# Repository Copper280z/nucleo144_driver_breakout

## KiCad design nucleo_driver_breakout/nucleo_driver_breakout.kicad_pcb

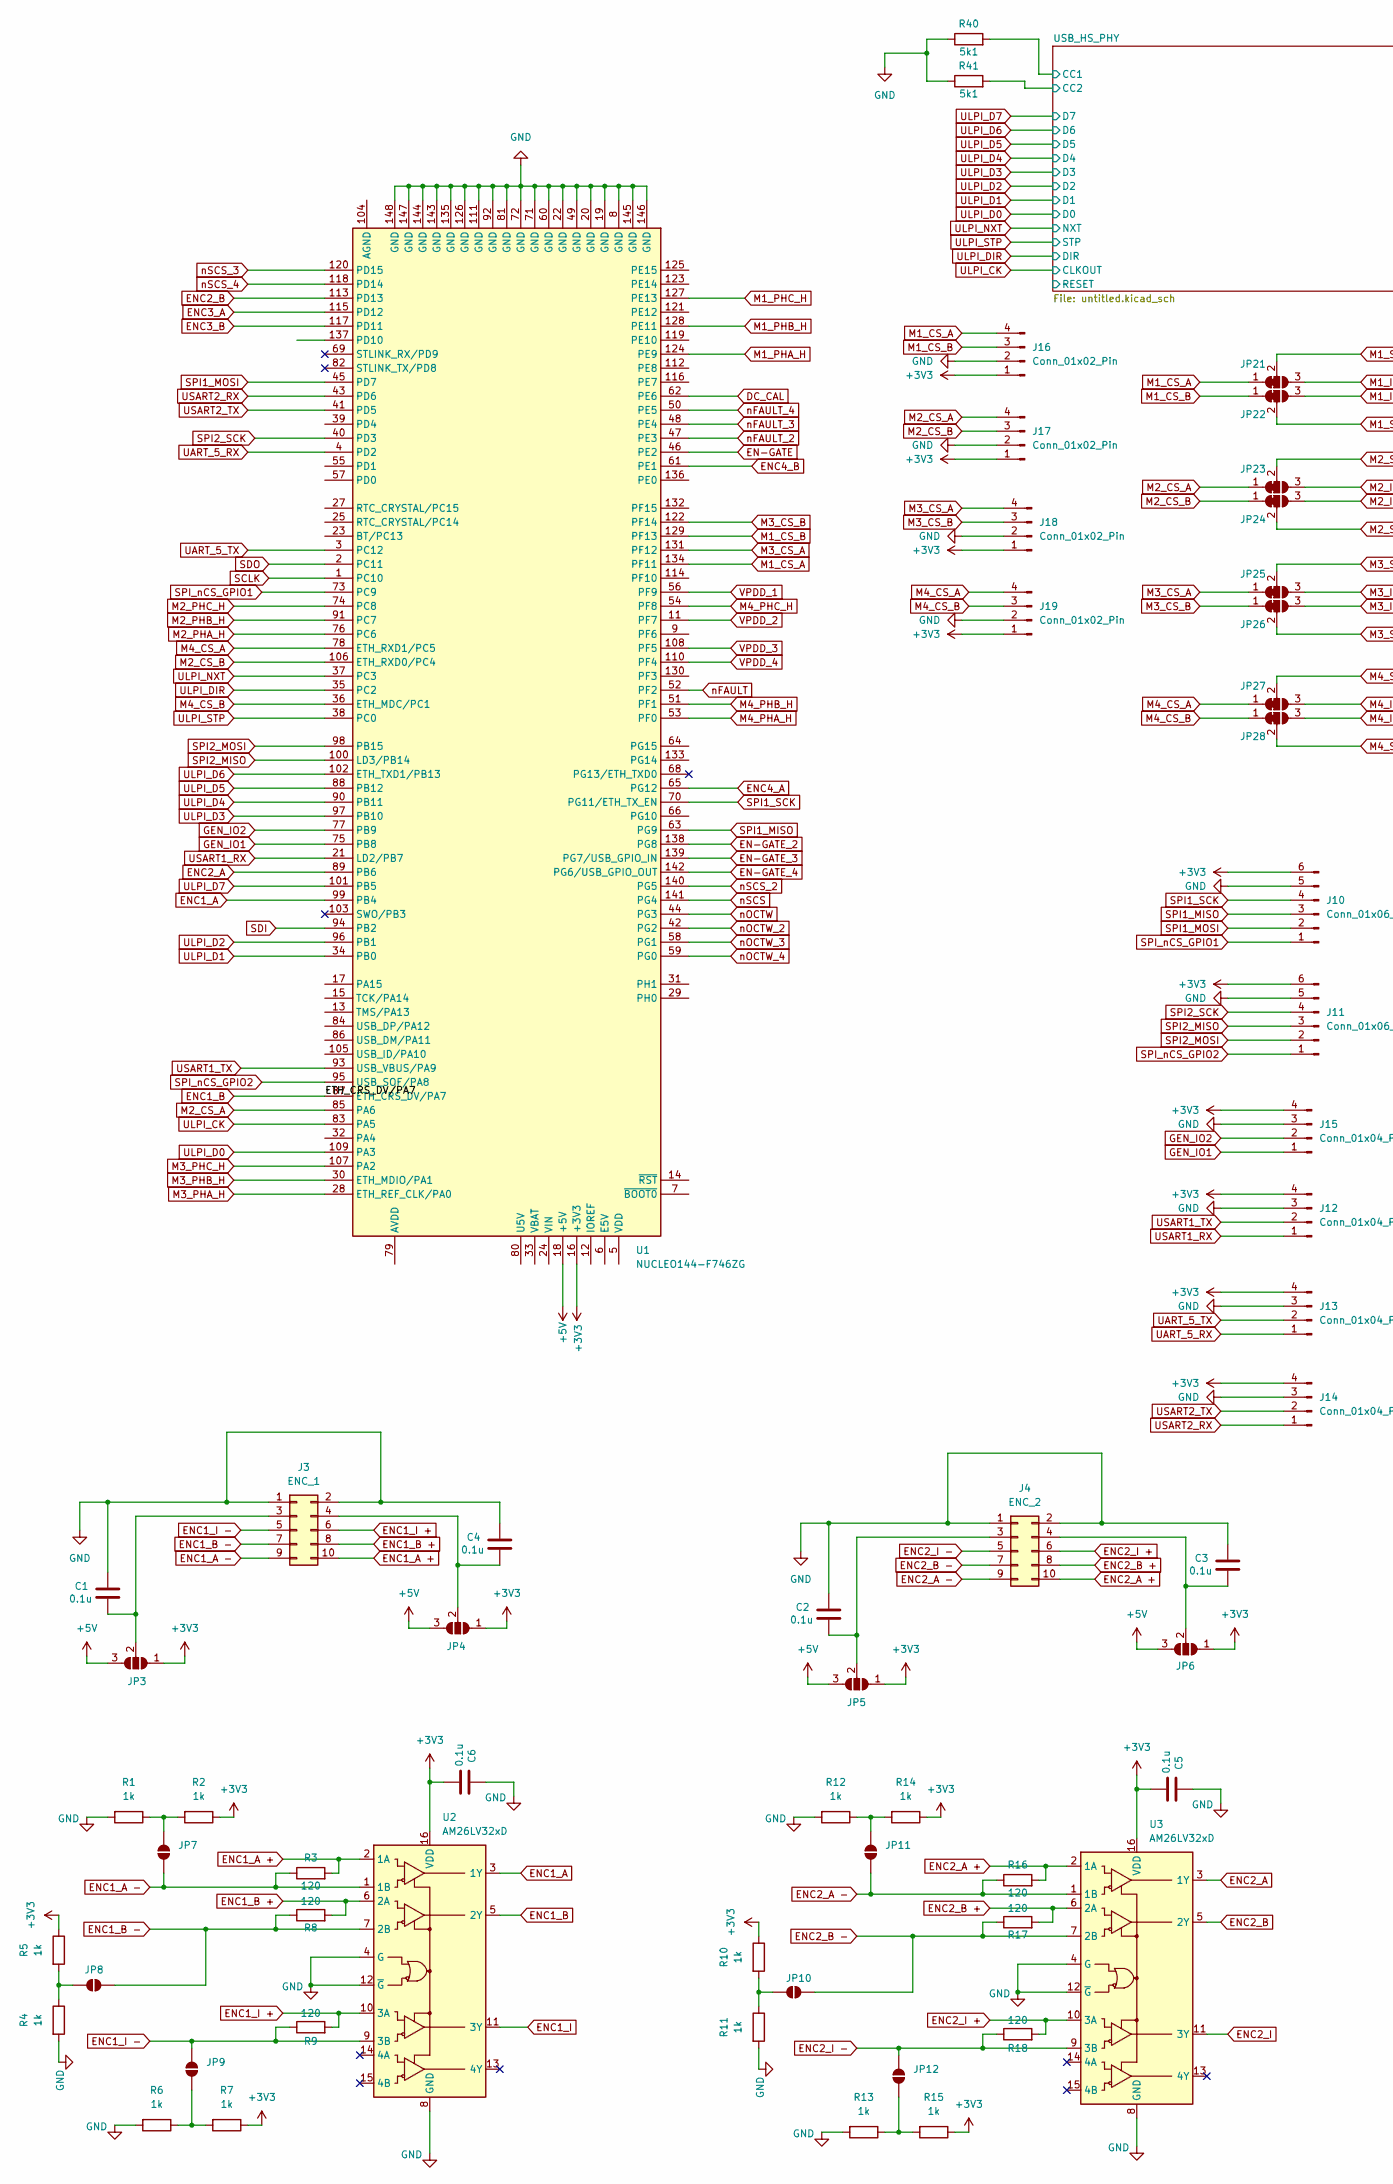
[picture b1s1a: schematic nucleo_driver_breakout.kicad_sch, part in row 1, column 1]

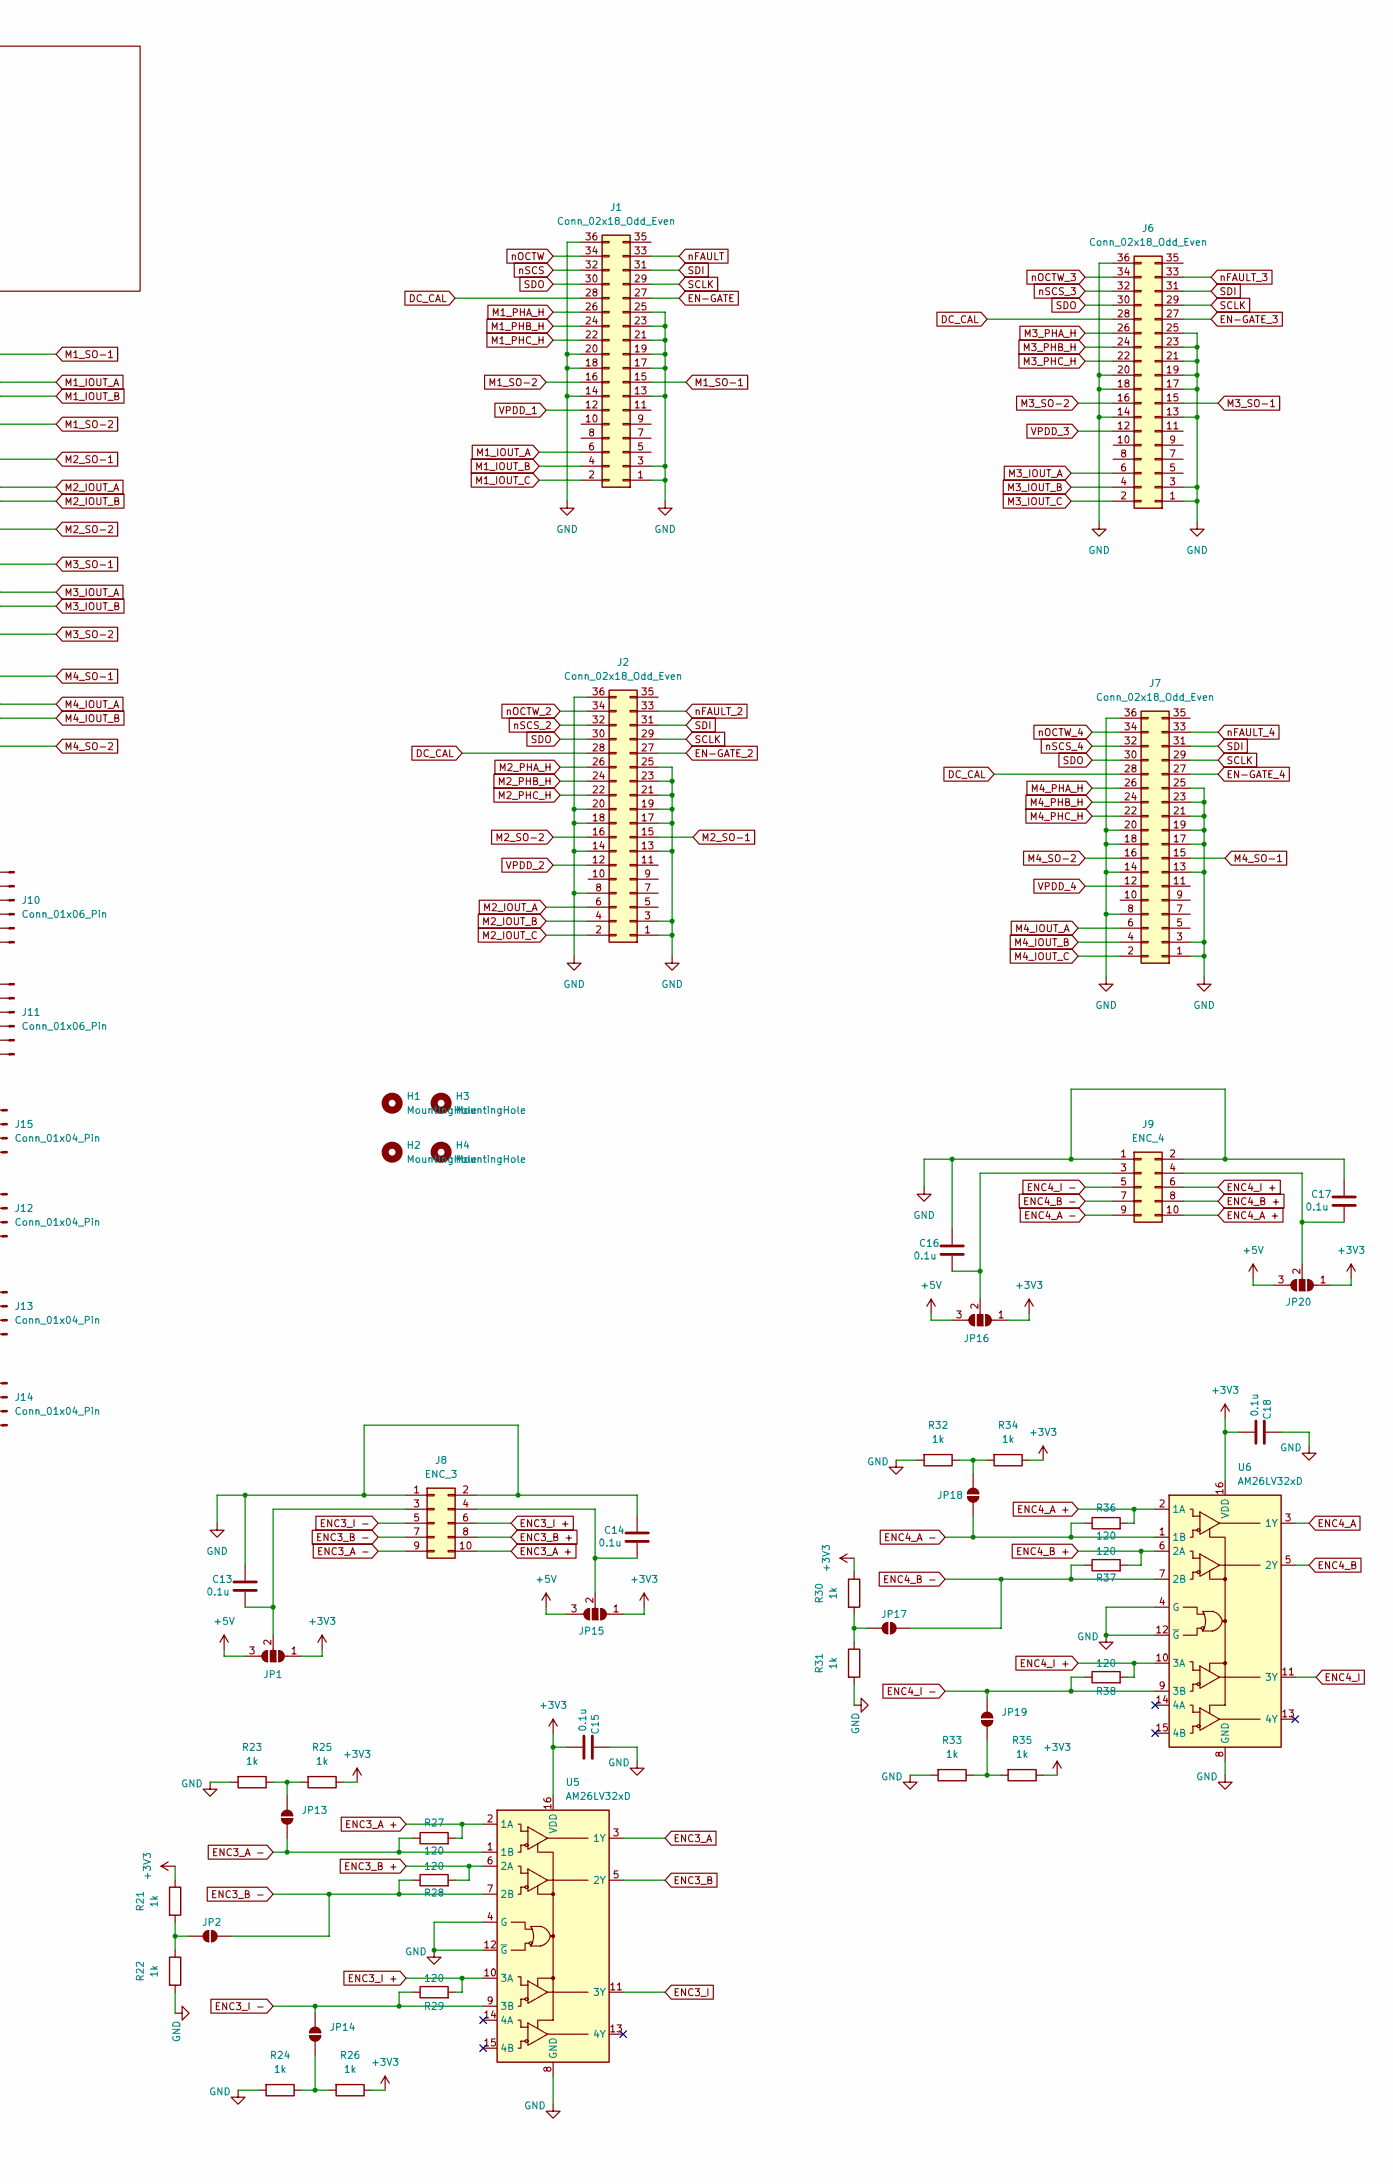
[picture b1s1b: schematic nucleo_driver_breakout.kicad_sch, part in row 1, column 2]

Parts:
C1, C2, C3, C4, C5, C6, C13, C14, C15, C16, C17, C18: 0.1u; C_0402_1005Metric; LCSC ID C1525
H1, H2, H3, H4: MountingHole; MountingHole_3.2mm_M3_ISO7380
J1, J2, J6, J7: Conn_02x18_Odd_Even; PinHeader_2x18_P2.54mm_Vertical
J3: ENC_1; PinHeader_2x05_P2.54mm_Vertical
J4: ENC_2; PinHeader_2x05_P2.54mm_Vertical
J8: ENC_3; PinHeader_2x05_P2.54mm_Vertical
J9: ENC_4; PinHeader_2x05_P2.54mm_Vertical
J10, J11: Conn_01x06_Pin; JST_EH_B6B-EH-A_1x06_P2.50mm_Vertical
J12, J13, J14, J15: Conn_01x04_Pin; JST_EH_B4B-EH-A_1x04_P2.50mm_Vertical
J16, J17, J18, J19: Conn_01x02_Pin; JST_EH_B4B-EH-A_1x04_P2.50mm_Vertical
JP1, JP3, JP4, JP5, JP6, JP15, JP16, JP20: SolderJumper_3_Open; SolderJumper-3_P1.3mm_Open_RoundedPad1.0x1.5mm
JP2, JP7, JP8, JP9, JP10, JP11, JP12, JP13, JP14, JP17, JP18, JP19: SolderJumper_2_Open; SolderJumper-2_P1.3mm_Open_RoundedPad1.0x1.5mm
JP21, JP22, JP23, JP24, JP25, JP26, JP27, JP28: SolderJumper_3_Bridged12; SolderJumper-3_P1.3mm_Bridged12_RoundedPad1.0x1.5mm
R1, R2, R4, R5, R6, R7, R10, R11, R12, R13, R14, R15, R21, R22, R23, R24, R25, R26, R30, R31, R32, R33, R34, R35: 1k; R_0402_1005Metric; LCSC ID C11702
R3, R8, R9, R16, R17, R18, R27, R28, R29, R36, R37, R38: 120; R_1206_3216Metric; LCSC ID C17909
R40: 5k1; R_0402_1005Metric; LCSC ID C25079
R41: 5k1; R_0402_1005Metric; LCSC ID C25905
U1: NUCLEO144-F746ZG; ST_Morpho_Connector_144_STLink
U2, U3, U5, U6: AM26LV32xD; SOIC-16_3.9x9.9mm_P1.27mm; LCSC ID C524786

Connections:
+3V3: C5.2, C6.2, C15.2, C18.2, J10.6, J11.6, J12.4, J13.4, J14.4, J15.4, J16.1, J17.1, J18.1, J19.1, JP1.1 (A), JP3.1 (A), JP4.1 (A), JP5.1 (A), JP6.1 (A), JP15.1 (A), JP16.1 (A), JP20.1 (A), R2.1, R5.1, R7.1, R10.1, R14.1, R15.1, R21.1, R25.1, R26.1, R30.1, R34.1, R35.1, U1.16 (+3V3), U2.16 (VDD), U3.16 (VDD), U5.16 (VDD), U6.16 (VDD); also elsewhere on the board
+5V: JP1.3 (B), JP3.3 (B), JP4.3 (B), JP5.3 (B), JP6.3 (B), JP15.3 (B), JP16.3 (B), JP20.3 (B), U1.18 (+5V)
/USB_HS_PHY/CC1: R40.2; also elsewhere on the board
/USB_HS_PHY/CC2: R41.2; also elsewhere on the board
DC_CAL: J1.28, J2.28, J6.28, J7.28, U1.62 (PE6)
EN-GATE: J1.27, U1.46 (PE2)
EN-GATE_2: J2.27, U1.138 (PG8)
EN-GATE_3: J6.27, U1.139 (PG7/USB_GPIO_IN)
EN-GATE_4: J7.27, U1.142 (PG6/USB_GPIO_OUT)
ENC1_A: U1.99 (PB4), U2.3 (1Y)
ENC1_A +: J3.10, R3.2, U2.2 (1A)
ENC1_A -: J3.9, JP7.1 (A), R3.1, U2.1 (1B)
ENC1_B: U1.87 (ETH_CRS_DV/PA7), U2.5 (2Y)
ENC1_B +: J3.8, R8.2, U2.6 (2A)
ENC1_B -: J3.7, JP8.1 (A), R8.1, U2.7 (2B)
ENC1_I: U2.11 (3Y)
ENC1_I +: J3.6, R9.2, U2.10 (3A)
ENC1_I -: J3.5, JP9.1 (A), R9.1, U2.9 (3B)
ENC2_A: U1.89 (PB6), U3.3 (1Y)
ENC2_A +: J4.10, R16.2, U3.2 (1A)
ENC2_A -: J4.9, JP11.1 (A), R16.1, U3.1 (1B)
ENC2_B: U1.113 (PD13), U3.5 (2Y)
ENC2_B +: J4.8, R17.2, U3.6 (2A)
ENC2_B -: J4.7, JP10.1 (A), R17.1, U3.7 (2B)
ENC2_I: U3.11 (3Y)
ENC2_I +: J4.6, R18.2, U3.10 (3A)
ENC2_I -: J4.5, JP12.1 (A), R18.1, U3.9 (3B)
ENC3_A: U1.115 (PD12), U5.3 (1Y)
ENC3_A +: J8.10, R27.2, U5.2 (1A)
ENC3_A -: J8.9, JP13.1 (A), R27.1, U5.1 (1B)
ENC3_B: U1.117 (PD11), U5.5 (2Y)
ENC3_B +: J8.8, R28.2, U5.6 (2A)
ENC3_B -: J8.7, JP2.1 (A), R28.1, U5.7 (2B)
ENC3_I: U5.11 (3Y)
ENC3_I +: J8.6, R29.2, U5.10 (3A)
ENC3_I -: J8.5, JP14.1 (A), R29.1, U5.9 (3B)
ENC4_A: U1.65 (PG12), U6.3 (1Y)
ENC4_A +: J9.10, R36.2, U6.2 (1A)
ENC4_A -: J9.9, JP18.1 (A), R36.1, U6.1 (1B)
ENC4_B: U1.61 (PE1), U6.5 (2Y)
ENC4_B +: J9.8, R37.2, U6.6 (2A)
ENC4_B -: J9.7, JP17.1 (A), R37.1, U6.7 (2B)
ENC4_I: U6.11 (3Y)
ENC4_I +: J9.6, R38.2, U6.10 (3A)
ENC4_I -: J9.5, JP19.1 (A), R38.1, U6.9 (3B)
GEN_IO1: J15.1, U1.75 (PB8)
GEN_IO2: J15.2, U1.77 (PB9)
GND: C1.1, C2.1, C3.1, C4.1, C5.1, C6.1, C13.1, C14.1, C15.1, C16.1, C17.1, C18.1, J1.1, J1.3, J1.13, J1.14, J1.17, J1.18, J1.19, J1.20, J1.21, J1.23, J1.25, J1.36, J2.1, J2.3, J2.8, J2.13, J2.14, J2.17, J2.18, J2.19, J2.20, J2.21, J2.23, J2.25, J2.36, J3.1, J3.2, J4.1, J4.2, J6.1, J6.3, J6.13, J6.14, J6.17, J6.18, J6.19, J6.20, J6.21, J6.23, J6.25, J6.36, J7.1, J7.3, J7.8, J7.13, J7.14, J7.17, J7.18, J7.19, J7.20, J7.21, J7.23, J7.25, J7.36, J8.1, J8.2, J9.1, J9.2, J10.5, J11.5, J12.3, J13.3, J14.3, J15.3, J16.2, J17.2, J18.2, J19.2, R1.2, R4.2, R6.2, R11.2, R12.2, R13.2, R22.2, R23.2, R24.2, R31.2, R32.2, R33.2, R40.1, R41.1, U1.8 (GND), U1.19 (GND), U1.20 (GND), U1.22 (GND), U1.49 (GND), U1.60 (GND), U1.71 (GND), U1.72 (GND), U1.81 (GND), U1.92 (GND), U1.111 (GND), U1.126 (GND), U1.135 (GND), U1.143 (GND), U1.144 (GND), U1.145 (GND), U1.146 (GND), U1.147 (GND), U1.148 (GND), U2.4 (G), U2.8 (GND), U2.12 (~G), U3.4 (G), U3.8 (GND), U3.12 (~G), U5.4 (G), U5.8 (GND), U5.12 (~G), U6.4 (G), U6.8 (GND), U6.12 (~G); also elsewhere on the board
M1_CS_A: J16.4, JP21.1 (A), U1.134 (PF11)
M1_CS_B: J16.3, JP22.1 (A), U1.129 (PF13)
M1_IOUT_A: J1.6, JP21.3 (B)
M1_IOUT_B: J1.4, JP22.3 (B)
M1_IOUT_C: J1.2
M1_PHA_H: J1.26, U1.124 (PE9)
M1_PHB_H: J1.24, U1.128 (PE11)
M1_PHC_H: J1.22, U1.127 (PE13)
M1_SO-1: J1.15, JP21.2 (C)
M1_SO-2: J1.16, JP22.2 (C)
M2_CS_A: J17.4, JP23.1 (A), U1.85 (PA6)
M2_CS_B: J17.3, JP24.1 (A), U1.106 (ETH_RXD0/PC4)
M2_IOUT_A: J2.6, JP23.3 (B)
M2_IOUT_B: J2.4, JP24.3 (B)
M2_IOUT_C: J2.2
M2_PHA_H: J2.26, U1.76 (PC6)
M2_PHB_H: J2.24, U1.91 (PC7)
M2_PHC_H: J2.22, U1.74 (PC8)
M2_SO-1: J2.15, JP23.2 (C)
M2_SO-2: J2.16, JP24.2 (C)
M3_CS_A: J18.4, JP25.1 (A), U1.131 (PF12)
M3_CS_B: J18.3, JP26.1 (A), U1.122 (PF14)
M3_IOUT_A: J6.6, JP25.3 (B)
M3_IOUT_B: J6.4, JP26.3 (B)
M3_IOUT_C: J6.2
M3_PHA_H: J6.26, U1.28 (ETH_REF_CLK/PA0)
M3_PHB_H: J6.24, U1.30 (ETH_MDIO/PA1)
M3_PHC_H: J6.22, U1.107 (PA2)
M3_SO-1: J6.15, JP25.2 (C)
M3_SO-2: J6.16, JP26.2 (C)
M4_CS_A: J19.4, JP27.1 (A), U1.78 (ETH_RXD1/PC5)
M4_CS_B: J19.3, JP28.1 (A), U1.36 (ETH_MDC/PC1)
M4_IOUT_A: J7.6, JP27.3 (B)
M4_IOUT_B: J7.4, JP28.3 (B)
M4_IOUT_C: J7.2
M4_PHA_H: J7.26, U1.53 (PF0)
M4_PHB_H: J7.24, U1.51 (PF1)
M4_PHC_H: J7.22, U1.54 (PF8)
M4_SO-1: J7.15, JP27.2 (C)
M4_SO-2: J7.16, JP28.2 (C)
unnamed: C1.2, J3.3, JP3.2 (C)
unnamed: C4.2, J3.4, JP4.2 (C)
unnamed: C2.2, J4.3, JP5.2 (C)
unnamed: C3.2, J4.4, JP6.2 (C)
unnamed: C13.2, J8.3, JP1.2 (C)
unnamed: C14.2, J8.4, JP15.2 (C)
unnamed: C16.2, J9.3, JP16.2 (C)
unnamed: C17.2, J9.4, JP20.2 (C)
unnamed: JP2.2 (B), R21.2, R22.1
unnamed: JP7.2 (B), R1.1, R2.2
unnamed: JP8.2 (B), R4.1, R5.2
unnamed: JP9.2 (B), R6.1, R7.2
unnamed: JP10.2 (B), R10.2, R11.1
unnamed: JP11.2 (B), R12.1, R14.2
unnamed: JP12.2 (B), R13.1, R15.2
unnamed: JP13.2 (B), R23.1, R25.2
unnamed: JP14.2 (B), R24.1, R26.2
unnamed: JP17.2 (B), R30.2, R31.1
unnamed: JP18.2 (B), R32.1, R34.2
unnamed: JP19.2 (B), R33.1, R35.2
SCLK: J1.29, J2.29, J6.29, J7.29, U1.1 (PC10)
SDI: J1.31, J2.31, J6.31, J7.31, U1.94 (PB2)
SDO: J1.30, J2.30, J6.30, J7.30, U1.2 (PC11)
SPI1_MISO: J10.3, U1.63 (PG9)
SPI1_MOSI: J10.2, U1.45 (PD7)
SPI1_SCK: J10.4, U1.70 (PG11/ETH_TX_EN)
SPI2_MISO: J11.3, U1.100 (LD3/PB14)
SPI2_MOSI: J11.2, U1.98 (PB15)
SPI2_SCK: J11.4, U1.40 (PD3)
SPI_nCS_GPIO1: J10.1, U1.73 (PC9)
SPI_nCS_GPIO2: J11.1, U1.95 (USB_SOF/PA8)
UART_5_RX: J13.1, U1.4 (PD2)
UART_5_TX: J13.2, U1.3 (PC12)
ULPI_CK: U1.83 (PA5); also elsewhere on the board
ULPI_D0: U1.109 (PA3); also elsewhere on the board
ULPI_D1: U1.34 (PB0); also elsewhere on the board
ULPI_D2: U1.96 (PB1); also elsewhere on the board
ULPI_D3: U1.97 (PB10); also elsewhere on the board
ULPI_D4: U1.90 (PB11); also elsewhere on the board
ULPI_D5: U1.88 (PB12); also elsewhere on the board
ULPI_D6: U1.102 (ETH_TXD1/PB13); also elsewhere on the board
ULPI_D7: U1.101 (PB5); also elsewhere on the board
ULPI_DIR: U1.35 (PC2); also elsewhere on the board
ULPI_NXT: U1.37 (PC3); also elsewhere on the board
ULPI_STP: U1.38 (PC0); also elsewhere on the board
USART1_RX: J12.1, U1.21 (LD2/PB7)
USART1_TX: J12.2, U1.93 (USB_VBUS/PA9)
USART2_RX: J14.1, U1.43 (PD6)
USART2_TX: J14.2, U1.41 (PD5)
VPDD_1: J1.12, U1.56 (PF9)
VPDD_2: J2.12, U1.11 (PF7)
VPDD_3: J6.12, U1.108 (PF5)
VPDD_4: J7.12, U1.110 (PF4)
nFAULT: J1.33, U1.52 (PF2)
nFAULT_2: J2.33, U1.47 (PE3)
nFAULT_3: J6.33, U1.48 (PE4)
nFAULT_4: J7.33, U1.50 (PE5)
nOCTW: J1.34, U1.44 (PG3)
nOCTW_2: J2.34, U1.42 (PG2)
nOCTW_3: J6.34, U1.58 (PG1)
nOCTW_4: J7.34, U1.59 (PG0)
nSCS: J1.32, U1.141 (PG4)
nSCS_2: J2.32, U1.140 (PG5)
nSCS_3: J6.32, U1.120 (PD15)
nSCS_4: J7.32, U1.118 (PD14)

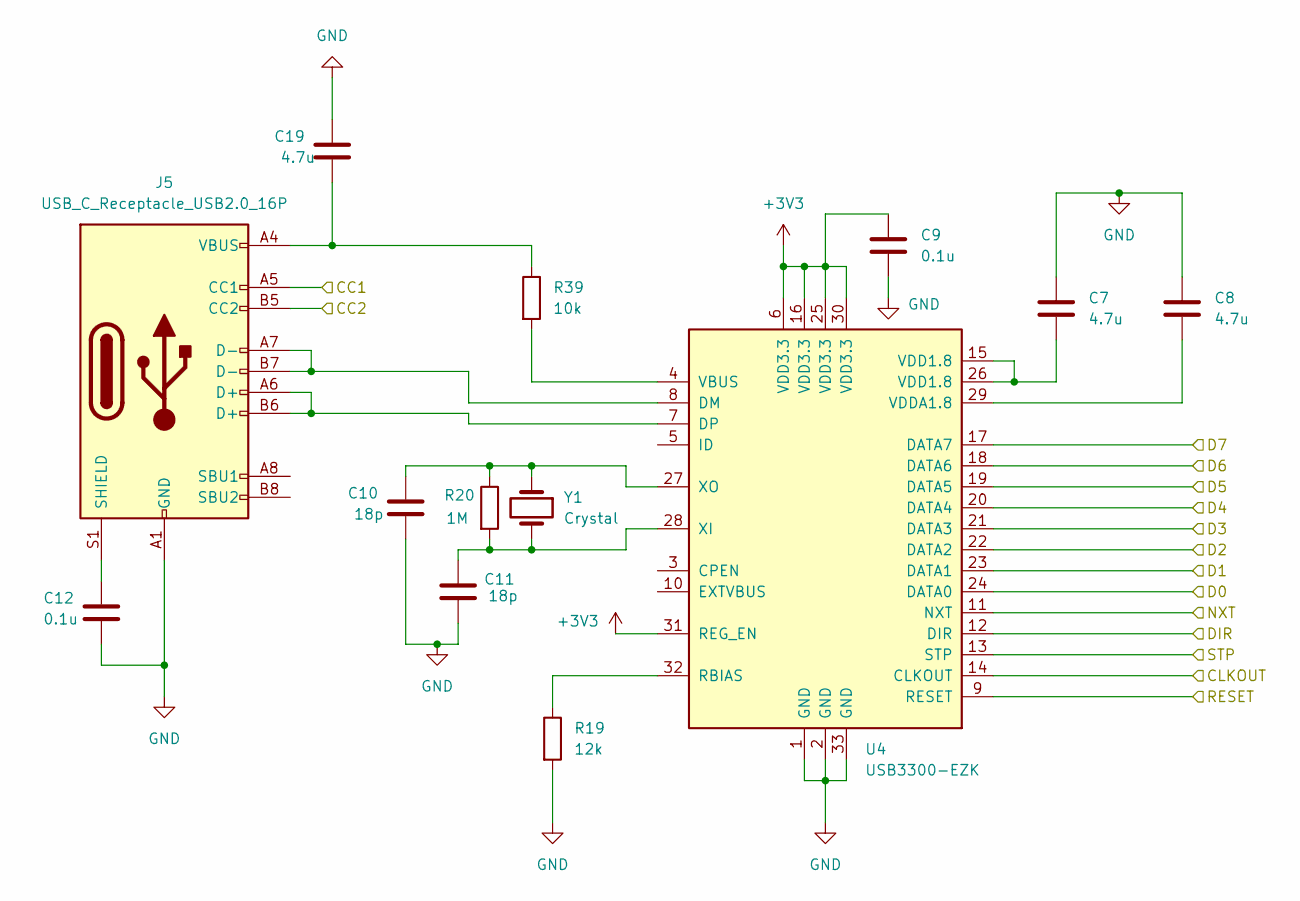
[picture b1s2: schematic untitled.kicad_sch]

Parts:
C7, C8: 4.7u; C_0402_1005Metric; LCSC ID C2858031
C9, C12: 0.1u; C_0402_1005Metric; LCSC ID C1525
C10, C11: 18p; C_0402_1005Metric; LCSC ID C1512022
C19: 4.7u; C_0402_1005Metric; LCSC ID C695126
J5: USB_C_Receptacle_USB2.0_16P; USB_C_Receptacle_G-Switch_GT-USB-7010ASV; LCSC ID C2988369
R19: 12k; R_0402_1005Metric; LCSC ID C25752
R20: 1M; R_0402_1005Metric
R39: 10k; R_0402_1005Metric; LCSC ID C25744
U4: USB3300-EZK; QFN-32-1EP_5x5mm_P0.5mm_EP3.45x3.45mm; LCSC ID C108383
Y1: Crystal; Crystal_SMD_Qantek_QC5CB-2Pin_5x3.2mm; LCSC ID C1985382

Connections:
+3V3: C9.1, U4.6 (VDD3.3), U4.16 (VDD3.3), U4.25 (VDD3.3), U4.30 (VDD3.3), U4.31 (REG_EN); also elsewhere on the board
/USB_HS_PHY/CC1: J5.A5 (CC1); also elsewhere on the board
/USB_HS_PHY/CC2: J5.B5 (CC2); also elsewhere on the board
/USB_HS_PHY/RESET: U4.9 (RESET)
GND: C7.1, C8.1, C9.2, C10.2, C11.2, C12.2, C19.1, J5.A1 (GND), J5.A12 (GND), J5.B1 (GND), J5.B12 (GND), R19.2, U4.1 (GND), U4.2 (GND), U4.33 (GND); also elsewhere on the board
unnamed: C7.2, U4.15 (VDD1.8), U4.26 (VDD1.8)
unnamed: C19.2, J5.A4 (VBUS), J5.A9 (VBUS), J5.B4 (VBUS), J5.B9 (VBUS), R39.1
unnamed: C12.1, J5.S1 (SHIELD)
unnamed: J5.A7 (D-), J5.B7 (D-), U4.8 (DM)
unnamed: J5.A6 (D+), J5.B6 (D+), U4.7 (DP)
unnamed: R19.1, U4.32 (RBIAS)
unnamed: R39.2, U4.4 (VBUS)
unnamed: C8.2, U4.29 (VDDA1.8)
unnamed: C11.1, R20.2, U4.28 (XI), Y1.2
unnamed: C10.1, R20.1, U4.27 (XO), Y1.1
ULPI_CK: U4.14 (CLKOUT); also elsewhere on the board
ULPI_D0: U4.24 (DATA0); also elsewhere on the board
ULPI_D1: U4.23 (DATA1); also elsewhere on the board
ULPI_D2: U4.22 (DATA2); also elsewhere on the board
ULPI_D3: U4.21 (DATA3); also elsewhere on the board
ULPI_D4: U4.20 (DATA4); also elsewhere on the board
ULPI_D5: U4.19 (DATA5); also elsewhere on the board
ULPI_D6: U4.18 (DATA6); also elsewhere on the board
ULPI_D7: U4.17 (DATA7); also elsewhere on the board
ULPI_DIR: U4.12 (DIR); also elsewhere on the board
ULPI_NXT: U4.11 (NXT); also elsewhere on the board
ULPI_STP: U4.13 (STP); also elsewhere on the board

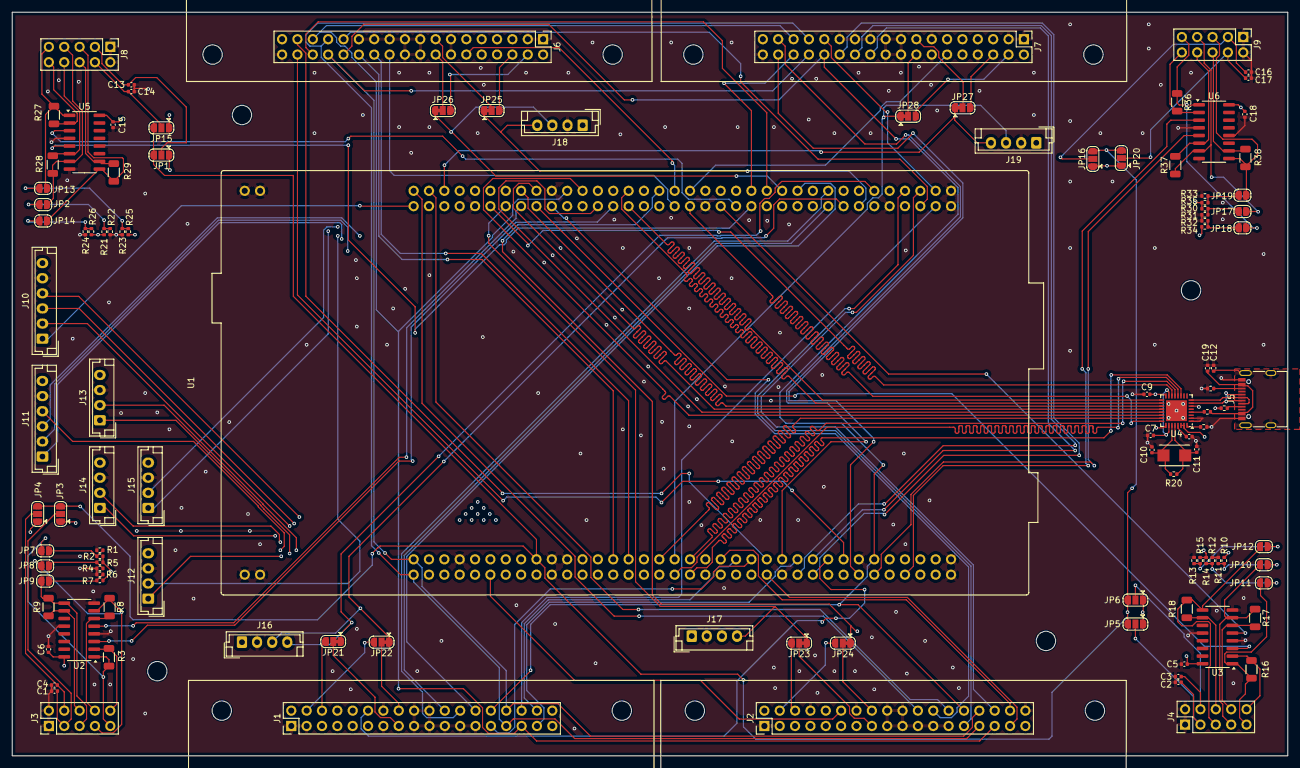
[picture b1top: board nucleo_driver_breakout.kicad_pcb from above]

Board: 4 copper layers, 211.0 x 123.0 mm, 118 parts (0 on the bottom side), 155 nets.

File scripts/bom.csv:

Designator,Value,Footprint,JLCPCB Part #
"C1,C2,C3,C4,C5,C6,C9,C12,C13,C14,C15,C16,C17,C18",0.1u,C0402,C1525
"C7,C8,C19",4.7u,C0402,-- mixed values --
"C10,C11",18p,C0402,C1512022
"J1,J2,J6,J7",Conn_02x18_Odd_Even,PinHeader_2x18_P2.54mm_Vertical,
J3,ENC_1,PinHeader_2x05_P2.54mm_Vertical,
J4,ENC_2,PinHeader_2x05_P2.54mm_Vertical,
J5,USB_C_Receptacle_USB2.0_16P,USB_C_Receptacle_G-Switch_GT-USB-7010ASV,C2988369
J8,ENC_3,PinHeader_2x05_P2.54mm_Vertical,
J9,ENC_4,PinHeader_2x05_P2.54mm_Vertical,
"J10,J11",Conn_01x06_Pin,JST_EH_B6B-EH-A_1x06_P2.50mm_Vertical,
"J12,J13,J14,J15",Conn_01x04_Pin,JST_EH_B4B-EH-A_1x04_P2.50mm_Vertical,
"J16,J17,J18,J19",Conn_01x02_Pin,JST_EH_B4B-EH-A_1x04_P2.50mm_Vertical,
"R1,R2,R4,R5,R6,R7,R10,R11,R12,R13,R14,R15,R21,R22,R23,R24,R25,R26,R30,R31,R32,R33,R34,R35",1k,R0402,C11702
"R3,R8,R9,R16,R17,R18,R27,R28,R29,R36,R37,R38",120,R0402,C25079
R19,12k,R0402,C25752
R20,1M,R0402,
R39,10k,R0402,C25744
"R40,R41",5k1,R0402,-- mixed values --
"U2,U3,U5,U6",AM26LV32xD,SOIC-16_3.9x9.9mm_P1.27mm,C524786
U4,USB3300-EZK,QFN-32-1EP_5x5mm_P0.5mm_EP3.45x3.45mm,C108383
Y1,Crystal,Crystal_SMD_Qantek_QC5CB-2Pin_5x3.2mm,C1985382

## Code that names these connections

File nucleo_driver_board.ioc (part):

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Mcu.Name=STM32H723ZGTx
Mcu.Package=LQFP144
Mcu.UserName=STM32H723ZGTx
PA0.GPIOParameters=GPIO_Label
PA0.GPIO_Label=M3_PHA_TIM2_CH1
PA0.Signal=S_TIM2_CH1_ETR
PA1.GPIOParameters=GPIO_Label
PA1.GPIO_Label=M3_PHB_TIM2_CH2
PA1.Signal=S_TIM2_CH2
PA13(JTMS/SWDIO).Mode=Trace_Asynchronous_SW
PA13(JTMS/SWDIO).Signal=DEBUG_JTMS-SWDIO
PA14(JTCK/SWCLK).Mode=Trace_Asynchronous_SW
PA14(JTCK/SWCLK).Signal=DEBUG_JTCK-SWCLK
PA15(JTDI).Signal=GPIO_Output
PA2.GPIOParameters=GPIO_Label
PA2.GPIO_Label=M3_PHC_TIM2_CH3
PA2.Signal=S_TIM2_CH3
PA3.Mode=Device_HS
PA3.Signal=USB_OTG_HS_ULPI_D0
PA5.Mode=Device_HS
PA5.Signal=USB_OTG_HS_ULPI_CK
PA6.GPIOParameters=GPIO_Label
PA6.GPIO_Label=M2_CS_A_ADC1_IN3
PA6.Signal=ADCx_INP3
PA7.GPIOParameters=GPIO_Label
PA7.GPIO_Label=ENC1_B_TIM3_CH2
PA7.Signal=S_TIM3_CH2
PA8.Signal=GPIO_Output
PA9.Mode=Asynchronous
PA9.Signal=USART1_TX
PB0.Mode=Device_HS
PB0.Signal=USB_OTG_HS_ULPI_D1
PB1.Mode=Device_HS
PB1.Signal=USB_OTG_HS_ULPI_D2
PB10.Mode=Device_HS
PB10.Signal=USB_OTG_HS_ULPI_D3
PB11.Mode=Device_HS
PB11.Signal=USB_OTG_HS_ULPI_D4
PB12.Mode=Device_HS
PB12.Signal=USB_OTG_HS_ULPI_D5
PB13.Mode=Device_HS
PB13.Signal=USB_OTG_HS_ULPI_D6
PB14.Mode=Full_Duplex_Master
PB14.Signal=SPI2_MISO
PB15.Mode=Full_Duplex_Master
PB15.Signal=SPI2_MOSI
PB2.GPIOParameters=GPIO_Label
PB2.GPIO_Label=MDRV_SDI_SPI3_MOSI
PB2.Mode=Full_Duplex_Master
PB2.Signal=SPI3_MOSI
PB3(JTDO/TRACESWO).Mode=Trace_Asynchronous_SW
PB3(JTDO/TRACESWO).Signal=DEBUG_JTDO-SWO
PB4(NJTRST).GPIOParameters=GPIO_Label
PB4(NJTRST).GPIO_Label=ENC1_A_TIM3_CH1
PB4(NJTRST).Signal=S_TIM3_CH1
PB5.Mode=Device_HS
PB5.Signal=USB_OTG_HS_ULPI_D7
PB6.GPIOParameters=GPIO_Label
PB6.GPIO_Label=ENC2_A_TIM4_CH1
PB6.Signal=S_TIM4_CH1
PB7.Mode=Asynchronous
PB7.Signal=USART1_RX
PC0.Mode=Device_HS
PC0.Signal=USB_OTG_HS_ULPI_STP
PC1.GPIOParameters=GPIO_Label
PC1.GPIO_Label=M4_CS_B_ADC2_IN11
PC1.Signal=ADCx_INP11
PC10.GPIOParameters=GPIO_Label
PC10.GPIO_Label=MDRV_SCLK_SPI3_SCK
PC10.Mode=Full_Duplex_Master
PC10.Signal=SPI3_SCK
PC11.GPIOParameters=GPIO_Label
PC11.GPIO_Label=MDRV_SDO_SPI3_MISO
PC11.Mode=Full_Duplex_Master
PC11.Signal=SPI3_MISO
PC12.Mode=Asynchronous
PC12.Signal=UART5_TX
PC13.GPIOParameters=GPIO_Label
PC13.GPIO_Label=USR_BTN
PC13.Signal=GPIO_Input
PC2_C.Mode=Device_HS
PC2_C.Signal=USB_OTG_HS_ULPI_DIR
PC3_C.Mode=Device_HS
PC3_C.Signal=USB_OTG_HS_ULPI_NXT
PC4.GPIOParameters=GPIO_Label
PC4.GPIO_Label=M2_CS_B_ADC2_IN4
PC4.Signal=ADCx_INP4
PC5.GPIOParameters=GPIO_Label
PC5.GPIO_Label=M4_CS_A_ADC1_IN8
PC5.Signal=ADCx_INP8
PC6.GPIOParameters=GPIO_Label
PC6.GPIO_Label=M2_PHA_TIM8_CH1
PC6.Signal=S_TIM8_CH1
PC7.GPIOParameters=GPIO_Label
PC7.GPIO_Label=M2_PHB_TIM8_CH2
PC7.Signal=S_TIM8_CH2
PC8.GPIOParameters=GPIO_Label
PC8.GPIO_Label=M2_PHC_TIM8_CH3
PC8.Signal=S_TIM8_CH3
PC9.GPIOParameters=GPIO_Label
PC9.GPIO_Label=AUX_SPI_nCS
PC9.Signal=GPIO_Output
PD0.Signal=GPIO_Output
PD1.Signal=GPIO_Output
PD11.GPIOParameters=GPIO_Label
PD11.GPIO_Label=ENC3_B_LPTIM2_IN2
PD11.Mode=Encoder_mode_occur1
PD11.Signal=LPTIM2_IN2
PD12.GPIOParameters=GPIO_Label
PD12.GPIO_Label=ENC3_A_LPTIM2_IN1
PD12.Mode=Encoder_mode_occur1
PD12.Signal=LPTIM2_IN1
PD13.GPIOParameters=GPIO_Label
PD13.GPIO_Label=ENC2_B_TIM4_CH2
PD13.Signal=S_TIM4_CH2
PD14.GPIOParameters=GPIO_Label
PD14.GPIO_Label=nSCS_4
PD14.Signal=GPIO_Output
PD15.GPIOParameters=GPIO_Label
PD15.GPIO_Label=nSCS_3
PD15.Signal=GPIO_Output
PD2.Mode=Asynchronous
PD2.Signal=UART5_RX
PD3.Mode=Full_Duplex_Master
PD3.Signal=SPI2_SCK
PD5.Mode=Asynchronous
PD5.Signal=USART2_TX
PD6.Mode=Asynchronous
PD6.Signal=USART2_RX
PD7.Mode=Full_Duplex_Master
PD7.Signal=SPI1_MOSI
PD8.Mode=Asynchronous
PD8.Signal=USART3_TX
PD9.Mode=Asynchronous
PD9.Signal=USART3_RX
PE1.GPIOParameters=GPIO_Label
PE1.GPIO_Label=ENC4_B_LPTIM1_IN2
PE1.Mode=Encoder_mode_occur1
PE1.Signal=LPTIM1_IN2
PE11.GPIOParameters=GPIO_Label
PE11.GPIO_Label=M1_PHB_TIM1_CH2
PE11.Signal=S_TIM1_CH2
PE13.GPIOParameters=GPIO_Label
PE13.GPIO_Label=M1_PHC_TIM1_CH3
PE13.Signal=S_TIM1_CH3
PE2.GPIOParameters=GPIO_Label
PE2.GPIO_Label=EN-GATE
PE2.Signal=GPIO_Output
PE3.GPIOParameters=GPIO_Label
PE3.GPIO_Label=nFAULT_2
PE3.Signal=GPIO_Input
PE4.GPIOParameters=GPIO_Label
PE4.GPIO_Label=nFAULT_3
PE4.Signal=GPIO_Input
PE5.GPIOParameters=GPIO_Label
PE5.GPIO_Label=nFAULT_4
PE5.Signal=GPIO_Input
PE6.GPIOParameters=GPIO_Label
PE6.GPIO_Label=DC_CAL
PE6.Signal=GPIO_Output
PE9.GPIOParameters=GPIO_Label
PE9.GPIO_Label=M1_PHA_TIM1_CH1
PE9.Signal=S_TIM1_CH1
PF0.GPIOParameters=GPIO_Label
PF0.GPIO_Label=M4_PHA_TIM23_CH1
PF0.Mode=PWM Generation1 CH1
PF0.Signal=TIM23_CH1
PF1.GPIOParameters=GPIO_Label
PF1.GPIO_Label=M4_PHA_TIM23_CH2
PF1.Signal=S_TIM23_CH2
PF11.GPIOParameters=GPIO_Label
PF11.GPIO_Label=M1_CS_A_ADC1_IN2
PF11.Mode=IN2-Single-Ended
PF11.Signal=ADC1_INP2
PF12.GPIOParameters=GPIO_Label
PF12.GPIO_Label=M3_CS_A_ADC1_IN6
PF12.Mode=IN6-Single-Ended
PF12.Signal=ADC1_INP6
PF13.GPIOParameters=GPIO_Label
PF13.GPIO_Label=M1_CS_B_ADC2_IN2
PF13.Mode=IN2-Single-Ended
PF13.Signal=ADC2_INP2
PF14.GPIOParameters=GPIO_Label
PF14.GPIO_Label=M3_CS_B_ADC2_IN6
PF14.Mode=IN6-Single-Ended
PF14.Signal=ADC2_INP6
PF2.GPIOParameters=GPIO_Label
PF2.GPIO_Label=nFAULT
PF2.Signal=GPIO_Input
PF3.GPIOParameters=GPIO_Label
PF3.GPIO_Label=VPDD_4_ADC3_IN5
PF3.Mode=IN5-Single-Ended
PF3.Signal=ADC3_INP5
PF5.GPIOParameters=GPIO_Label
PF5.GPIO_Label=VPDD_3_ADC3_IN4
PF5.Mode=IN4-Single-Ended
PF5.Signal=ADC3_INP4
PF7.GPIOParameters=GPIO_Label
PF7.GPIO_Label=VPDD_2_ADC3_IN3
PF7.Mode=IN3-Single-Ended
PF7.Signal=ADC3_INP3
PF9.GPIOParameters=GPIO_Label
PF9.GPIO_Label=VPDD_1_ADC3_IN2
PF9.Mode=IN2-Single-Ended
PF9.Signal=ADC3_INP2
PG0.Signal=GPIO_Input
PG1.GPIOParameters=GPIO_Label
PG1.GPIO_Label=nOCTW_3
PG1.Signal=GPIO_Input
PG11.Mode=Full_Duplex_Master
PG11.Signal=SPI1_SCK
PG12.GPIOParameters=GPIO_Label
PG12.GPIO_Label=ENC4_A_LPTIM1_IN1
PG12.Mode=Encoder_mode_occur1
PG12.Signal=LPTIM1_IN1
PG14.GPIOParameters=GPIO_Label
PG14.GPIO_Label=M4_PHC_TIM23_CH3
PG14.Signal=S_TIM23_CH3
PG2.GPIOParameters=GPIO_Label
PG2.GPIO_Label=nOCTW_2
PG2.Signal=GPIO_Input
PG3.GPIOParameters=GPIO_Label
PG3.GPIO_Label=nOCTW
PG3.Signal=GPIO_Input
PG4.GPIOParameters=GPIO_Label
PG4.GPIO_Label=nSCS
PG4.Signal=GPIO_Output
PG5.Signal=GPIO_Output
PG6.GPIOParameters=GPIO_Label
PG6.GPIO_Label=EN-GATE_4
PG6.Signal=GPIO_Output
PG7.GPIOParameters=GPIO_Label
PG7.GPIO_Label=EN-GATE_3
PG7.Signal=GPIO_Output
PG8.GPIOParameters=GPIO_Label
PG8.GPIO_Label=EN-GATE_2
PG8.Signal=GPIO_Output
PG9.Mode=Full_Duplex_Master
PG9.Signal=SPI1_MISO
RCC.SYSCLKFreq_VALUE=544000000
RCC.SYSCLKSource=RCC_SYSCLKSOURCE_PLLCLK
board=custom

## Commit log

2024-06-12 first board rev
2024-06-12 added current sense header for each motor
2024-06-12 changed usb connector and added LCSC IDs
2024-06-13 added bolt holes, vias, and fixed some silkscreen overlaps
2024-06-16 changed termination resistors to 1206 and added gitignore
2024-08-08 usb demo
